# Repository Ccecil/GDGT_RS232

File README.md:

This is a Gadgeteer to RS232 adapter board based on the MAX3232.  It is intended for use with the Smoothieboard V2 but has breakouts for generic use. 

Schematic available here: [RS232_GDGT.pdf](https://github.com/user-attachments/files/24160931/RS232_GDGT.pdf)

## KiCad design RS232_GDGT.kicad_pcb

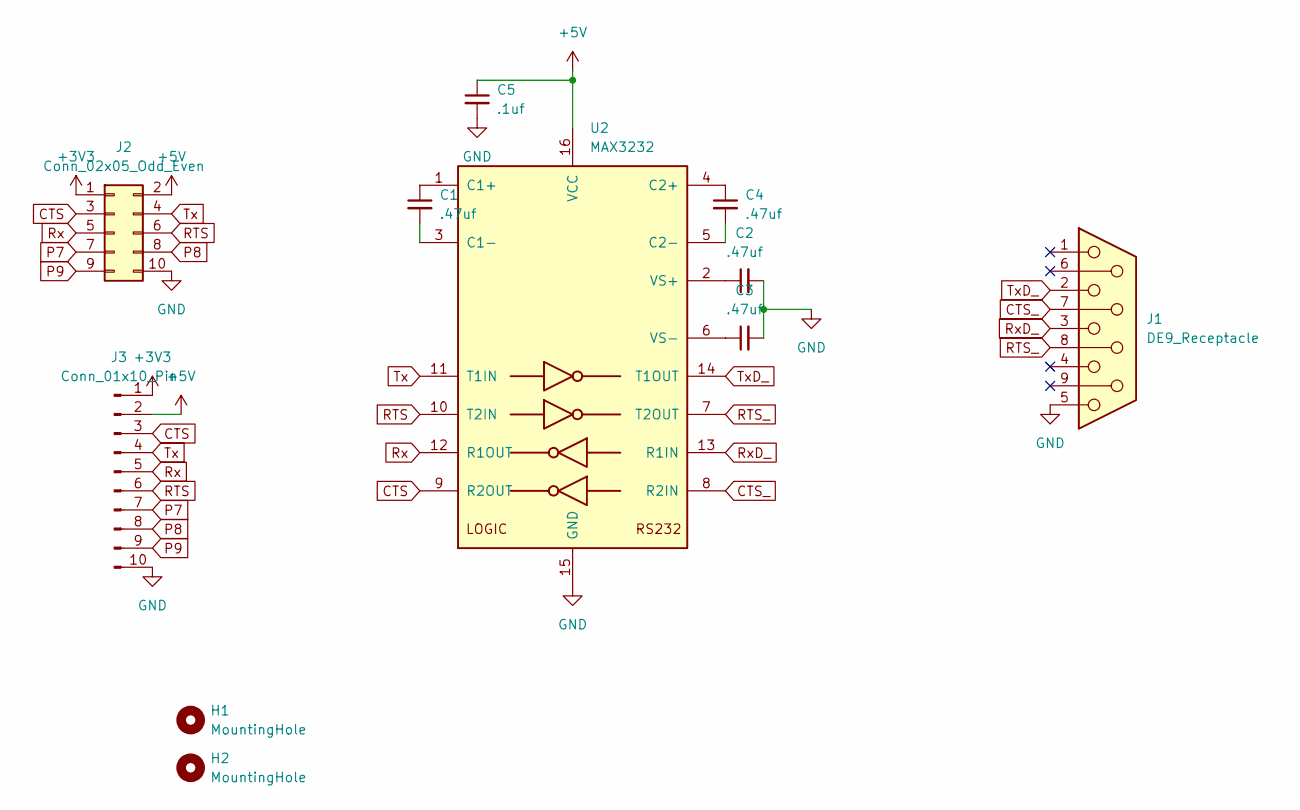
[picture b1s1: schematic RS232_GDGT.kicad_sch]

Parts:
C1, C2, C3, C4: .47uf; C_0402_1005Metric
C5: .1uf; C_0402_1005Metric
H1, H2: MountingHole; MountingHole_3.2mm_M3
J1: DE9_Receptacle; DSUB-9_Female_Horizontal_P2.77x2.84mm_EdgePinOffset4.94mm_H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
J2: Conn_02x05_Odd_Even; PinHeader_2x05_P1.27mm_Vertical_SMD
J3: Conn_01x10_Pin; PinHeader_1x10_P2.54mm_Vertical
U2: MAX3232; TSSOP-16_4.4x5mm_P0.65mm

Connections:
+3V3: J2.1, J3.1
+5V: C5.1, J2.2, J3.2, U2.16 (VCC)
CTS: J2.3, J3.3, U2.9 (R2OUT)
CTS_: J1.7, U2.8 (R2IN)
GND: C2.2, C3.2, C5.2, J1.5, J2.10, J3.10, U2.15 (GND)
unnamed: C1.1, U2.1 (C1+)
unnamed: C1.2, U2.3 (C1-)
unnamed: C4.1, U2.4 (C2+)
unnamed: C4.2, U2.5 (C2-)
unnamed: C2.1, U2.2 (VS+)
unnamed: C3.1, U2.6 (VS-)
P7: J2.7, J3.7
P8: J2.8, J3.8
P9: J2.9, J3.9
RTS: J2.6, J3.6, U2.10 (T2IN)
RTS_: J1.8, U2.7 (T2OUT)
Rx: J2.5, J3.5, U2.12 (R1OUT)
RxD_: J1.3, U2.13 (R1IN)
Tx: J2.4, J3.4, U2.11 (T1IN)
TxD_: J1.2, U2.14 (T1OUT)

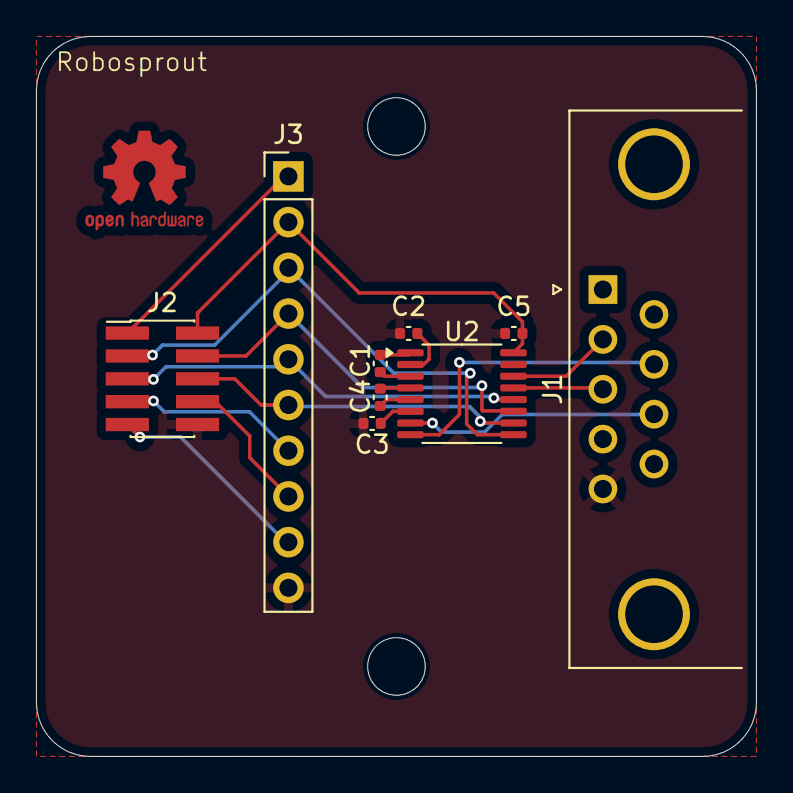
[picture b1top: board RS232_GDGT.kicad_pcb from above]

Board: 2 copper layers, 40.0 x 40.0 mm, 11 parts (0 on the bottom side), 20 nets.

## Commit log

2025-12-15 Initial upload
